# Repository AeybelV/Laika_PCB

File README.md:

# Laika Flight Computer

A modular fight computer PCB centered around the Raspberry Pi Zero 2

# Components
- Processor: Raspberry Pi Zero 2 W
- IMU: STMicroelectronics LSM6DSLTR
- Magnetometer: Memsic MMC5983MA
- Barometer: TE Connectivity MS5611

# KiCad Libraries
- https://www.snapeda.com/parts/RASPBERRY%20PI%20ZERO%202%20W/Raspberry%20Pi/view-part/?welcome=home
- https://www.snapeda.com/parts/MMC5983MA/Memsic%20Inc./view-part/
- https://www.amphenol-cs.com/product/10106813021112lf.html

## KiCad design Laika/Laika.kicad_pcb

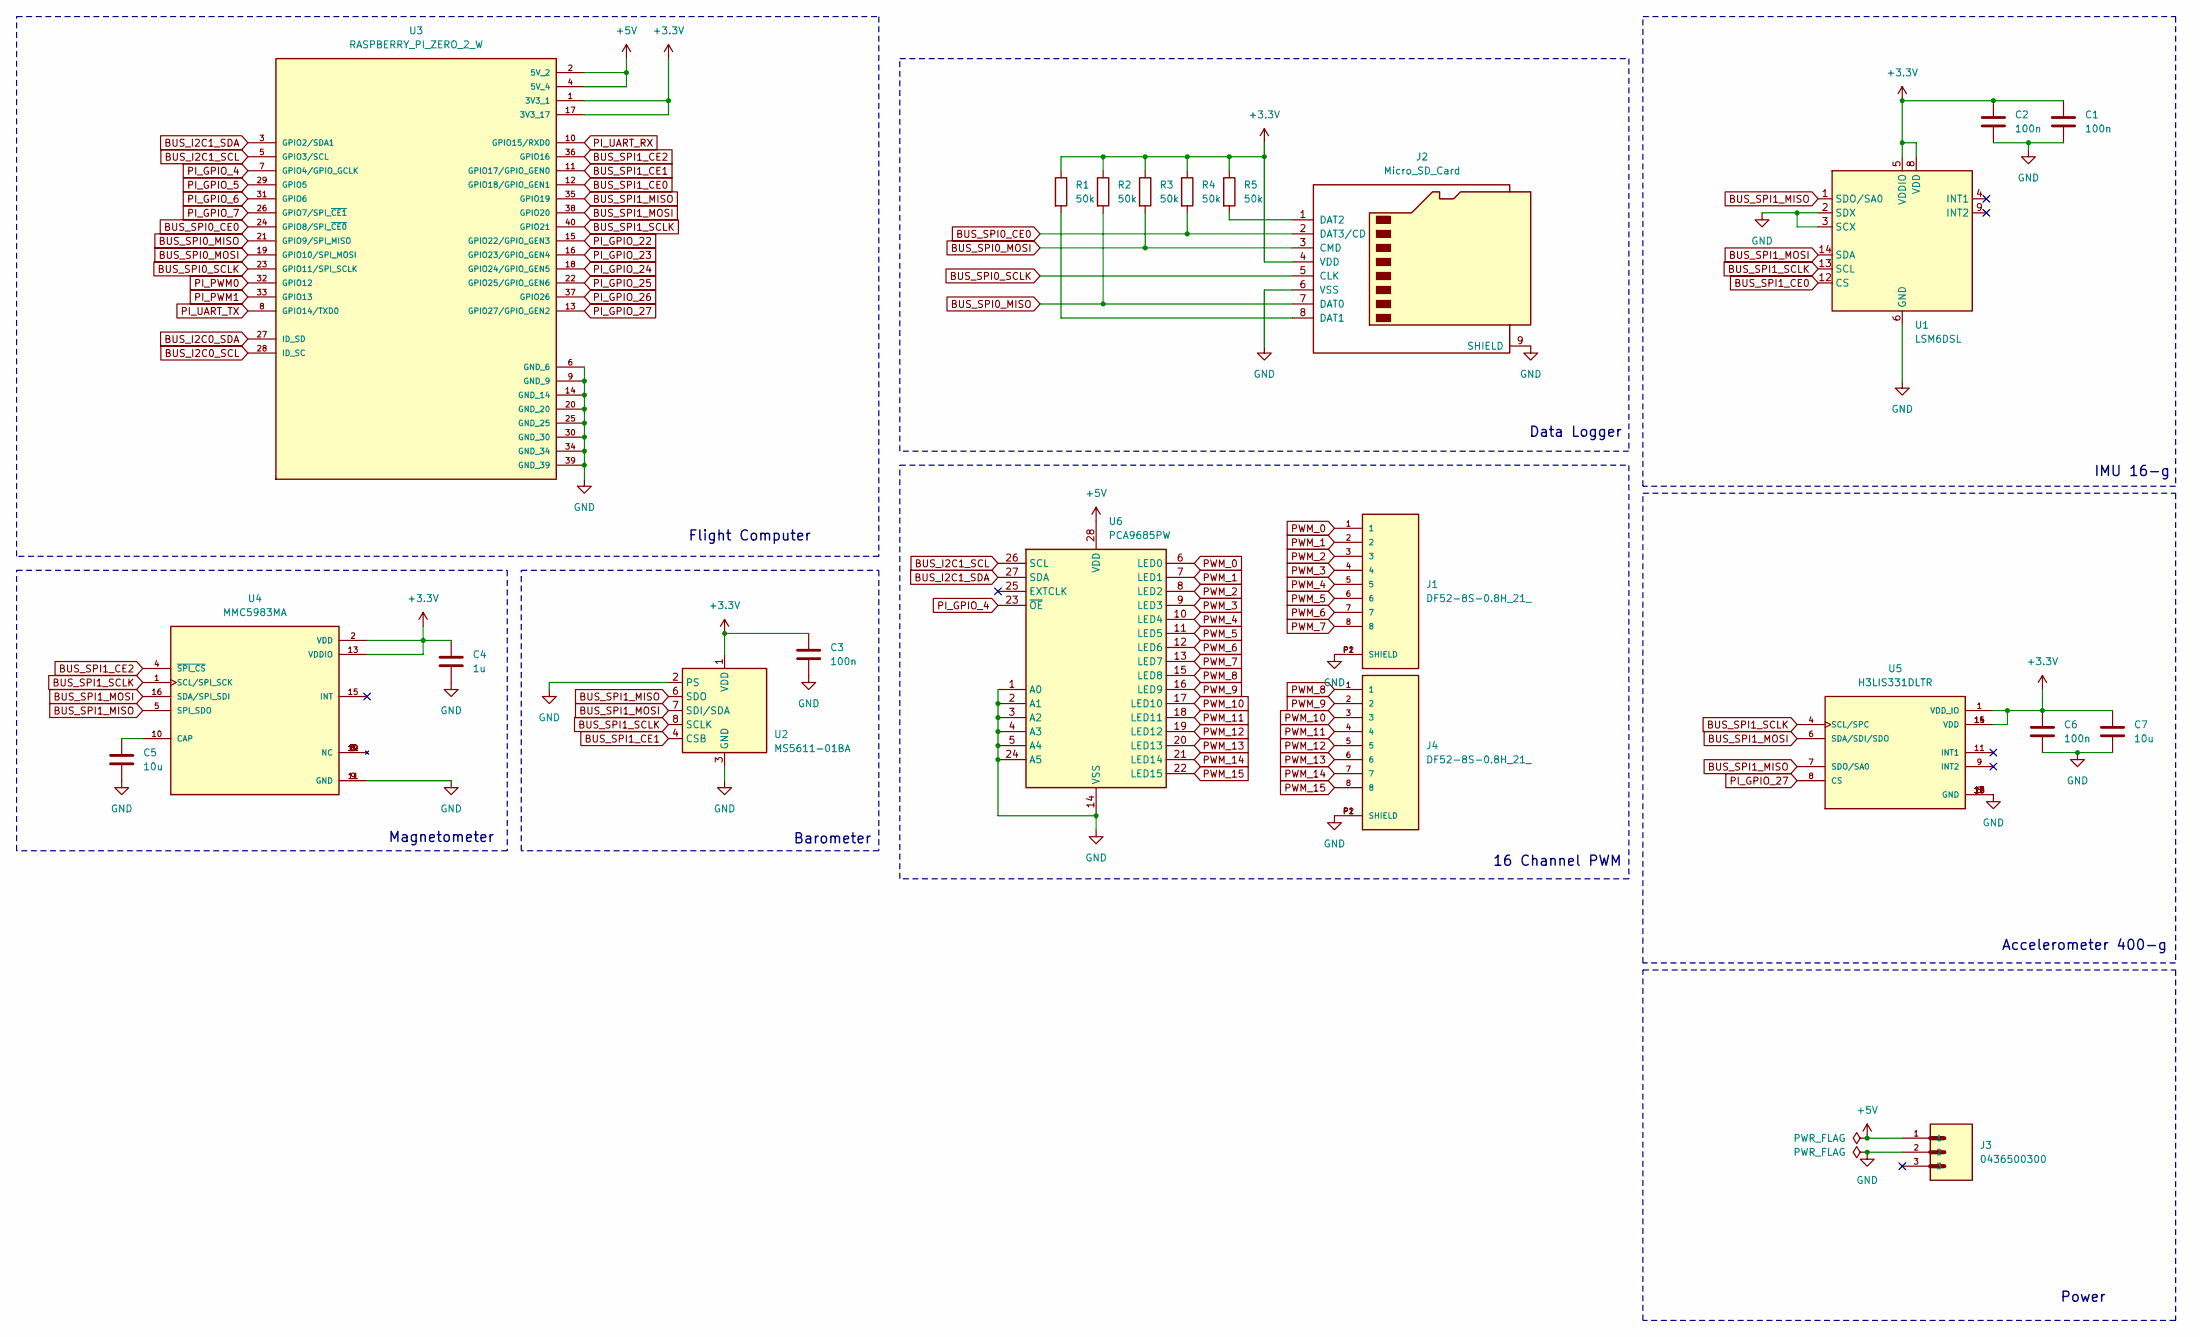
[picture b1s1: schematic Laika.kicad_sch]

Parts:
C1, C2, C3, C6: 100n; C_0603_1608Metric
C4: 1u; C_0603_1608Metric
C5, C7: 10u; C_0603_1608Metric
J1, J4: DF52-8S-0.8H_21_; HIROSE_DF52-8S-0.8H_21_; PARTREV May 2018
J2: Micro_SD_Card; microSD_HC_Molex_47219-2001
J3: 0436500300; MOLEX_0436500300
R1, R2, R3, R4, R5: 50k; R_1206_3216Metric
U1: LSM6DSL; LGA-14_3x2.5mm_P0.5mm_LayoutBorder3x4y
U2: MS5611-01BA; LGA-8_3x5mm_P1.25mm
U3: RASPBERRY_PI_ZERO_2_W; MODULE_RASPBERRY_PI_ZERO_2_W; PARTREV April 2024
U4: MMC5983MA; MMC5983_PQFN50; PARTREV A
U5: H3LIS331DLTR; QFN300X300X100-16N
U6: PCA9685PW; TSSOP-28_4.4x9.7mm_P0.65mm

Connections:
+3.3V: C1.1, C2.1, C3.1, C4.1, C6.1, C7.1, J2.4 (VDD), R1.1, R2.1, R3.1, R4.1, R5.1, U1.5 (VDDIO), U1.8 (VDD), U2.1 (VDD), U3.1 (3V3_1), U3.17 (3V3_17), U4.2 (VDD), U4.13 (VDDIO), U5.1 (VDD_IO), U5.14 (VDD), U5.15 (VDD)
+5V: J3.1, U3.2 (5V_2), U3.4 (5V_4), U6.28 (VDD)
BUS_I2C0_SCL: U3.28 (ID_SC)
BUS_I2C0_SDA: U3.27 (ID_SD)
BUS_I2C1_SCL: U3.5 (GPIO3/SCL), U6.26 (SCL)
BUS_I2C1_SDA: U3.3 (GPIO2/SDA1), U6.27 (SDA)
BUS_SPI0_CE0: J2.2 (DAT3/CD), R4.2, U3.24 (GPIO8/SPI_~CE0)
BUS_SPI0_MISO: J2.7 (DAT0), R2.2, U3.21 (GPIO9/SPI_MISO)
BUS_SPI0_MOSI: J2.3 (CMD), R3.2, U3.19 (GPIO10/SPI_MOSI)
BUS_SPI0_SCLK: J2.5 (CLK), U3.23 (GPIO11/SPI_SCLK)
BUS_SPI1_CE0: U1.12 (CS), U3.12 (GPIO18/GPIO_GEN1)
BUS_SPI1_CE1: U2.4 (CSB), U2.5 (CSB), U3.11 (GPIO17/GPIO_GEN0)
BUS_SPI1_CE2: U3.36 (GPIO16), U4.4 (~SPI_CS)
BUS_SPI1_MISO: U1.1 (SDO/SA0), U2.6 (SDO), U3.35 (GPIO19), U4.5 (SPI_SDO), U5.7 (SDO/SA0)
BUS_SPI1_MOSI: U1.14 (SDA), U2.7 (SDI/SDA), U3.38 (GPIO20), U4.16 (SDA/SPI_SDI), U5.6 (SDA/SDI/SDO)
BUS_SPI1_SCLK: U1.13 (SCL), U2.8 (SCLK), U3.40 (GPIO21), U4.1 (SCL/SPI_SCK), U5.4 (SCL/SPC)
GND: C1.2, C2.2, C3.2, C4.2, C5.2, C6.2, C7.2, J1.P1 (SHIELD), J1.P2 (SHIELD), J2.6 (VSS), J2.9 (SHIELD), J3.2, J4.P1 (SHIELD), J4.P2 (SHIELD), U1.2 (SDX), U1.3 (SCX), U1.6 (GND), U1.7 (GND), U2.2 (PS), U2.3 (GND), U3.6 (GND_6), U3.9 (GND_9), U3.14 (GND_14), U3.20 (GND_20), U3.25 (GND_25), U3.30 (GND_30), U3.34 (GND_34), U3.39 (GND_39), U4.9 (GND), U4.11 (GND), U5.5 (GND), U5.10 (GND), U5.12 (GND), U5.13 (GND), U5.16 (GND), U6.1 (A0), U6.2 (A1), U6.3 (A2), U6.4 (A3), U6.5 (A4), U6.14 (VSS), U6.24 (A5)
unnamed: J2.8 (DAT1), R1.2
unnamed: J2.1 (DAT2), R5.2
unnamed: C5.1, U4.10 (CAP)
PI_GPIO_4: U3.7 (GPIO4/GPIO_GCLK), U6.23 (~OE)
PI_GPIO_5: U3.29 (GPIO5)
PI_GPIO_6: U3.31 (GPIO6)
PI_GPIO_7: U3.26 (GPIO7/SPI_~CE1)
PI_GPIO_22: U3.15 (GPIO22/GPIO_GEN3)
PI_GPIO_23: U3.16 (GPIO23/GPIO_GEN4)
PI_GPIO_24: U3.18 (GPIO24/GPIO_GEN5)
PI_GPIO_25: U3.22 (GPIO25/GPIO_GEN6)
PI_GPIO_26: U3.37 (GPIO26)
PI_GPIO_27: U3.13 (GPIO27/GPIO_GEN2), U5.8 (CS)
PI_PWM0: U3.32 (GPIO12)
PI_PWM1: U3.33 (GPIO13)
PI_UART_RX: U3.10 (GPIO15/RXD0)
PI_UART_TX: U3.8 (GPIO14/TXD0)
PWM_0: J1.1, U6.6 (LED0)
PWM_1: J1.2, U6.7 (LED1)
PWM_2: J1.3, U6.8 (LED2)
PWM_3: J1.4, U6.9 (LED3)
PWM_4: J1.5, U6.10 (LED4)
PWM_5: J1.6, U6.11 (LED5)
PWM_6: J1.7, U6.12 (LED6)
PWM_7: J1.8, U6.13 (LED7)
PWM_8: J4.1, U6.15 (LED8)
PWM_9: J4.2, U6.16 (LED9)
PWM_10: J4.3, U6.17 (LED10)
PWM_11: J4.4, U6.18 (LED11)
PWM_12: J4.5, U6.19 (LED12)
PWM_13: J4.6, U6.20 (LED13)
PWM_14: J4.7, U6.21 (LED14)
PWM_15: J4.8, U6.22 (LED15)

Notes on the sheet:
Barometer
Power
Magnetometer
16 Channel PWM
Flight Computer
IMU 16-g
Accelerometer 400-g
Data Logger

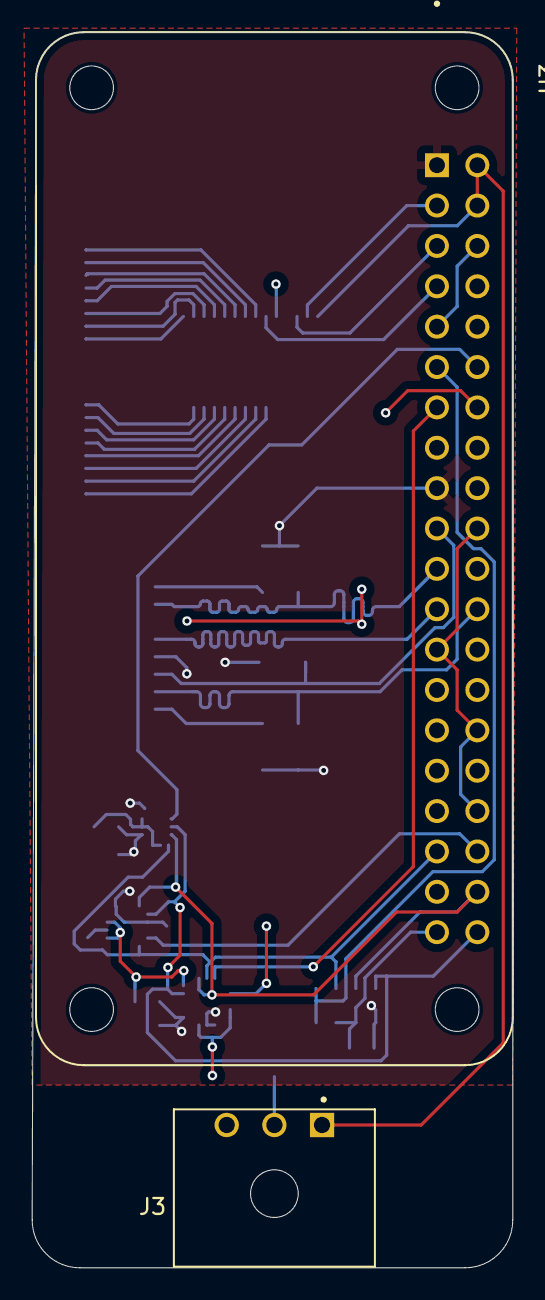
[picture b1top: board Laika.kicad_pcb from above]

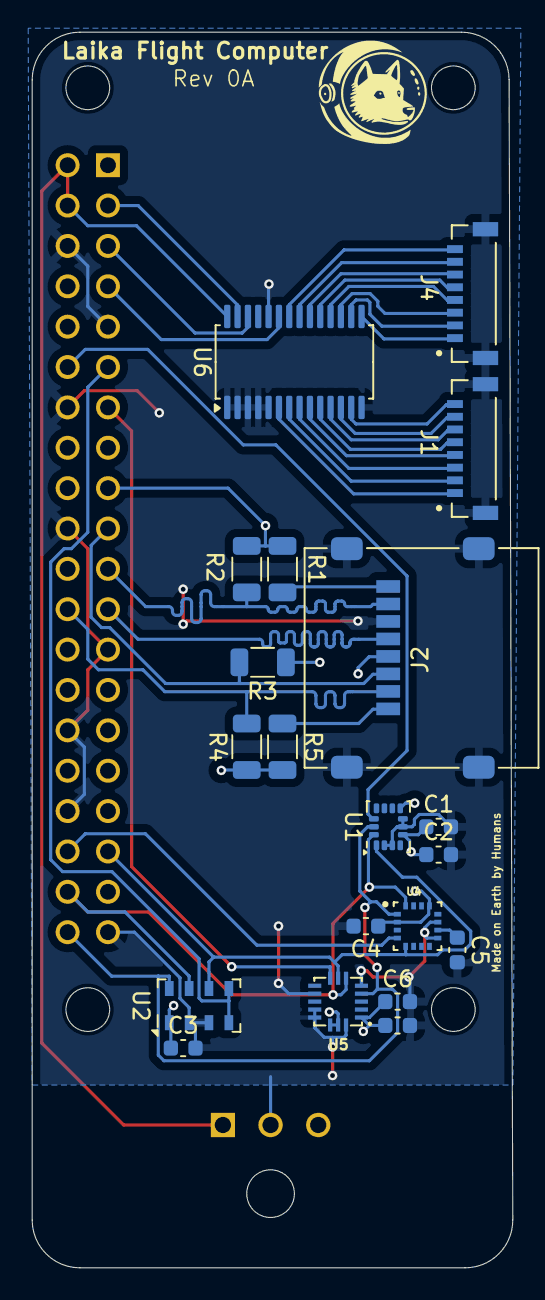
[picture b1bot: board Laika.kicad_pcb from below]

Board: 2 copper layers, 30.2 x 77.8 mm, 22 parts (20 on the bottom side), 36 nets.

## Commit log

2024-09-30 Initial workings on schematic
2024-09-30 Schematic for sensors
2024-10-01 RS485 hookup, new accelerometer, connectors, edgecuts
2024-11-03 Version 0A
2024-11-12 Updated gitignore
